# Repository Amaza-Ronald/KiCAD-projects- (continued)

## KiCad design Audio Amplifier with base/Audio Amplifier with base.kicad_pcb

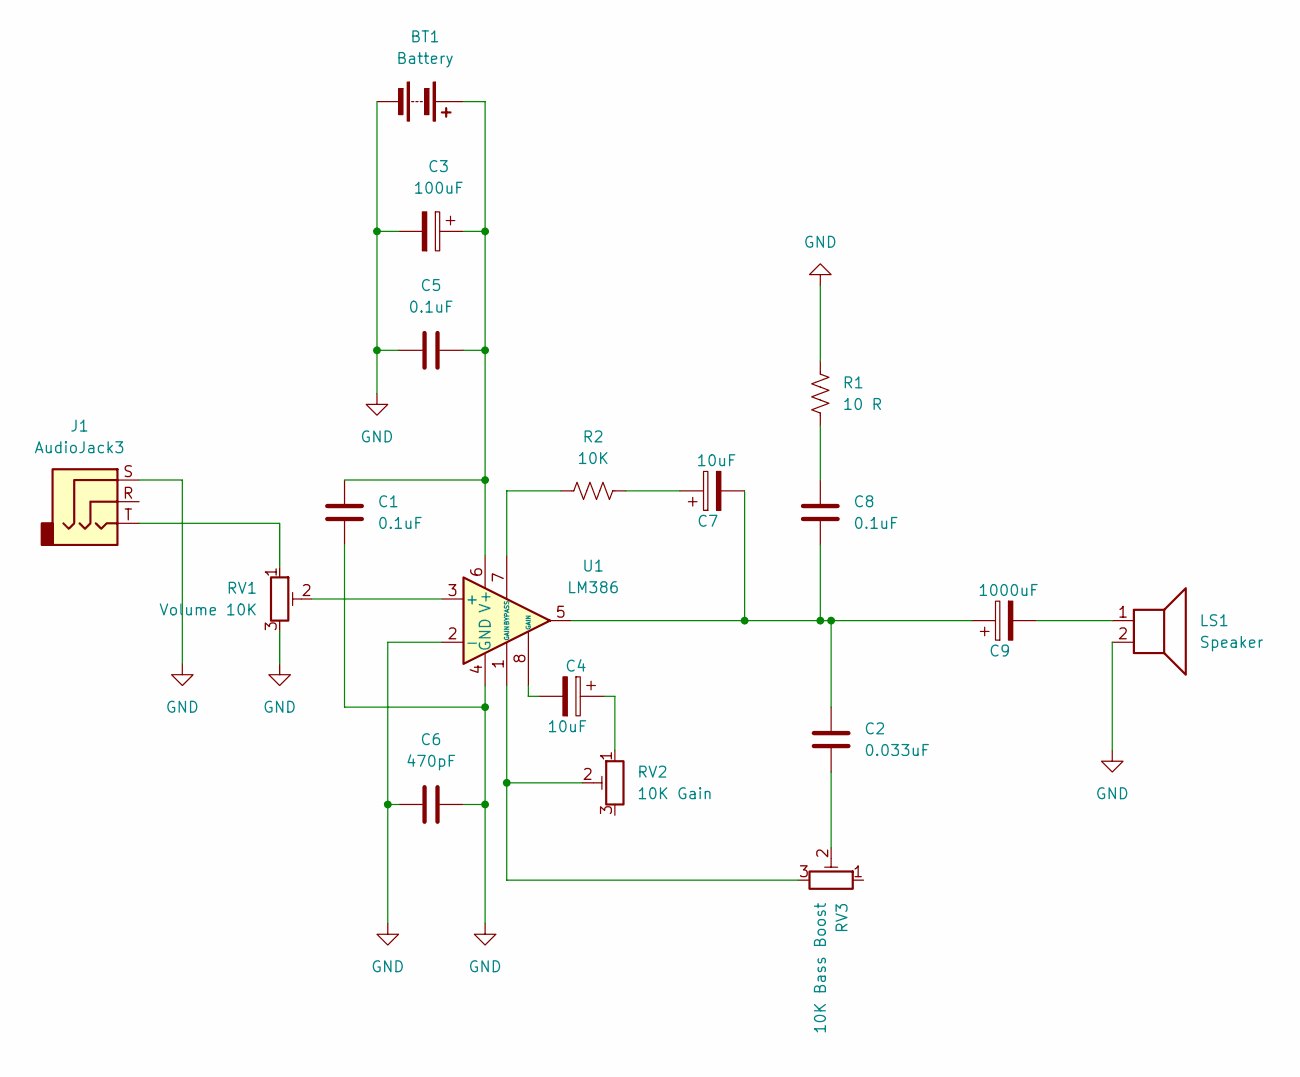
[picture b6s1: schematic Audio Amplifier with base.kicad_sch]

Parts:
BT1: Battery; Battery_Panasonic_CR1025-VSK_Vertical_CircularHoles
C1, C5, C8: 0.1uF; C_Disc_D16.0mm_W5.0mm_P7.50mm
C2: 0.033uF; C_Disc_D16.0mm_W5.0mm_P7.50mm
C3: 100uF; CP_Radial_D8.0mm_P3.50mm
C4, C7: 10uF; CP_Radial_D8.0mm_P3.50mm
C6: 470pF; C_Disc_D16.0mm_W5.0mm_P7.50mm
C9: 1000uF; CP_Radial_D8.0mm_P3.50mm
J1: AudioJack3; Jack_3.5mm_CUI_SJ1-3513N_Horizontal
LS1: Speaker; TerminalBlock_bornier-2_P5.08mm
R1: 10 R; R_Axial_DIN0207_L6.3mm_D2.5mm_P7.62mm_Horizontal
R2: 10K; R_Axial_DIN0207_L6.3mm_D2.5mm_P7.62mm_Horizontal
RV1: Volume 10K; Potentiometer_Bourns_3266X_Horizontal
RV2: 10K Gain; Potentiometer_Bourns_3266X_Horizontal
RV3: 10K Bass Boost; Potentiometer_Bourns_3266X_Horizontal
U1: LM386; DIP-8_W7.62mm_Socket_LongPads

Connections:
GND: BT1.2 (-), C1.2, C3.2, C5.2, C6.1, C6.2, J1.S, LS1.2, R1.2, RV1.3, U1.2 (-), U1.4 (GND)
unnamed: BT1.1 (+), C1.1, C3.1, C5.1, U1.6 (V+)
unnamed: C2.1, RV3.2
unnamed: C2.2, C7.2, C8.2, C9.1, U1.5
unnamed: C4.1, RV2.1
unnamed: C4.2, U1.8 (GAIN)
unnamed: C7.1, R2.1
unnamed: C8.1, R1.1
unnamed: C9.2, LS1.1
unnamed: J1.T, RV1.1
unnamed: RV2.2, RV3.3, U1.1 (GAIN)
unnamed: RV1.2, U1.3 (+)
unnamed: R2.2, U1.7 (BYPASS)

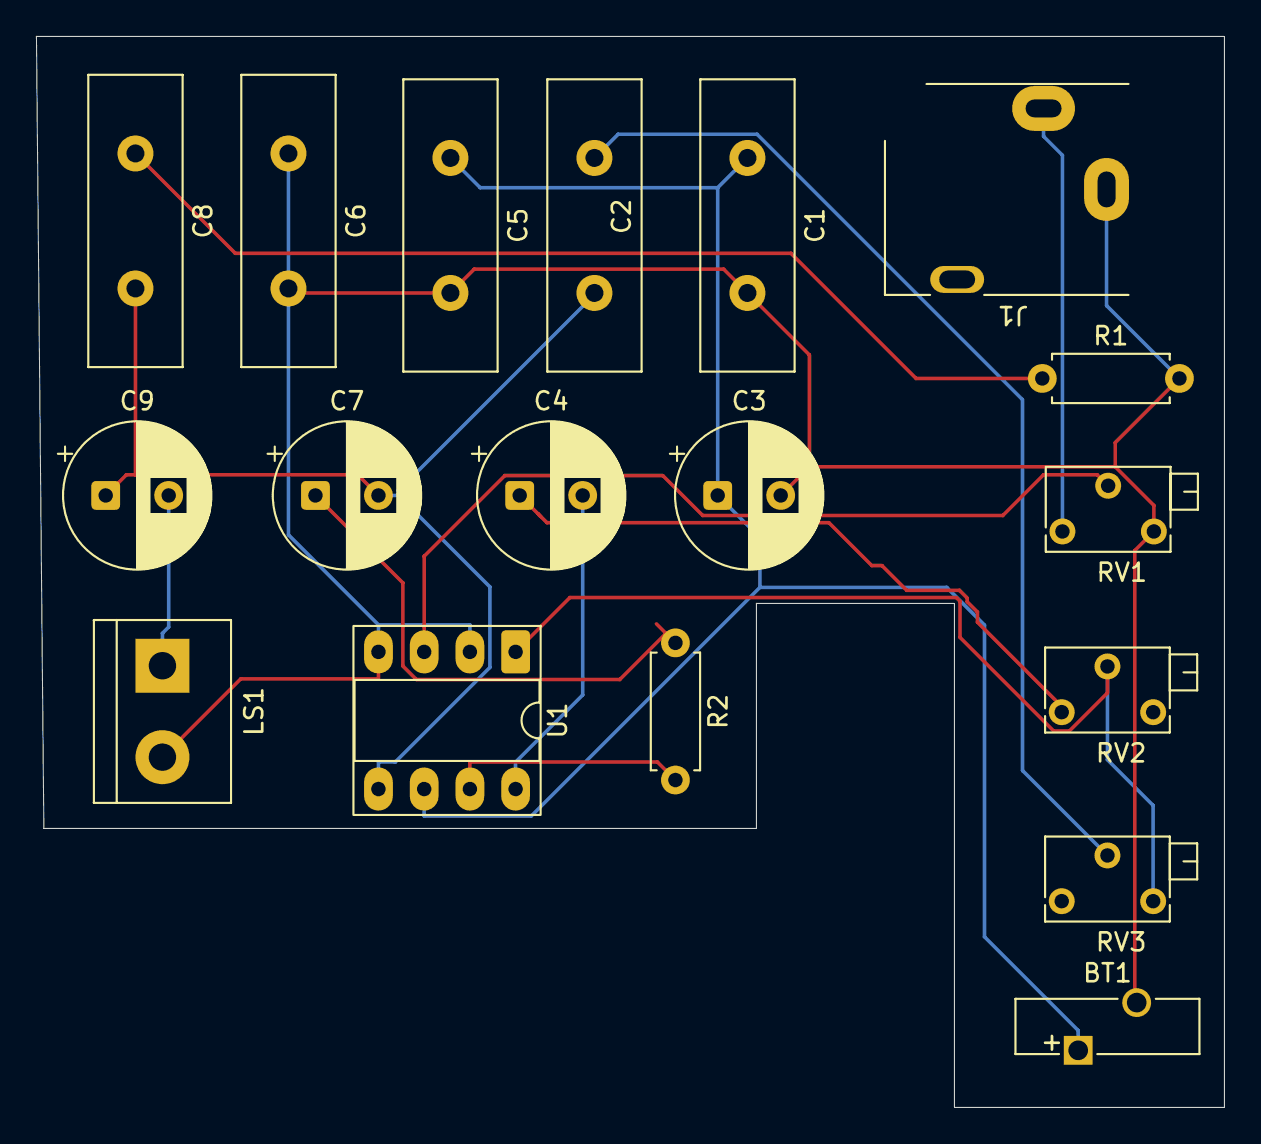
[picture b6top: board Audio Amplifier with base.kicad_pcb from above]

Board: 2 copper layers, 66.0 x 59.5 mm, 18 parts (0 on the bottom side), 13 nets.

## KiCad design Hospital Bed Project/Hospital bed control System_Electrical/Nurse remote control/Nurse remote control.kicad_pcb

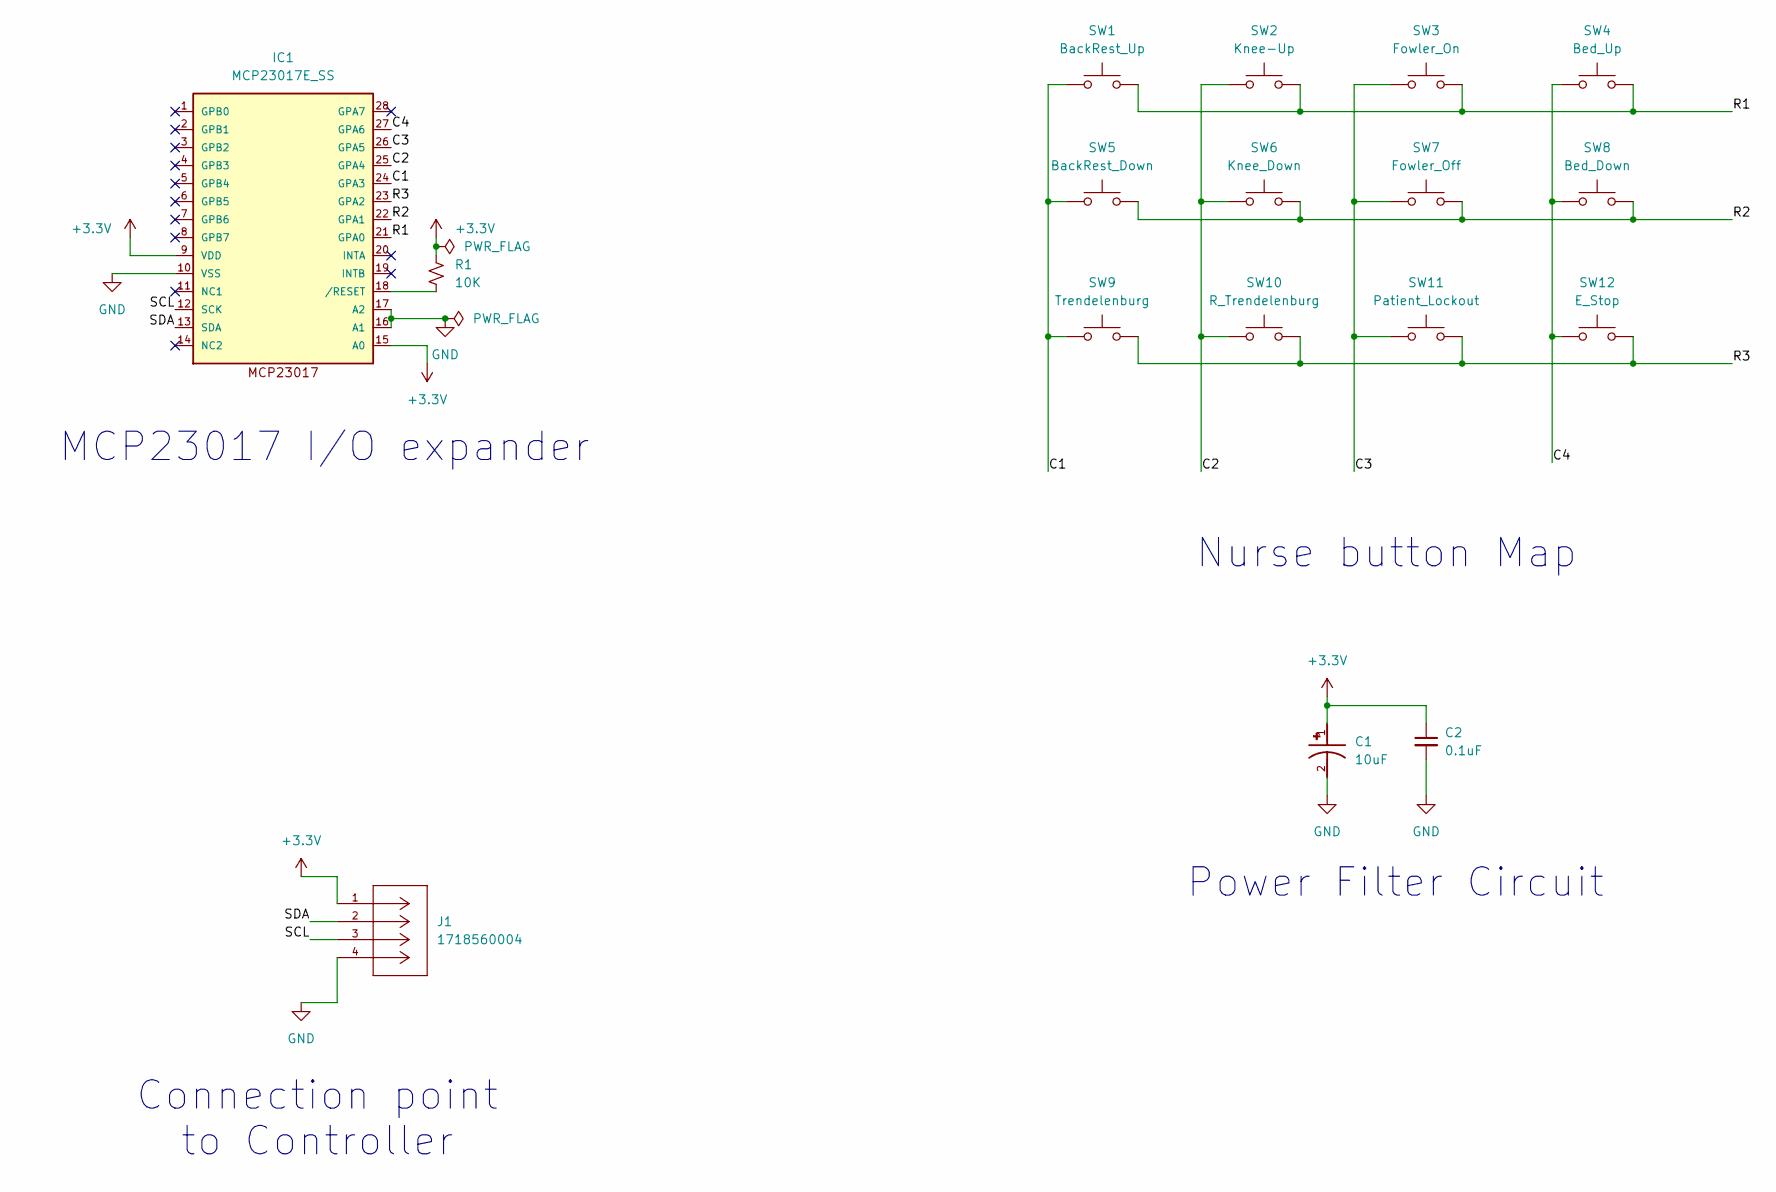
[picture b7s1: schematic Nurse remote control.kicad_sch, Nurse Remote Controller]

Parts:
C1: 10uF; CAP_EEFSX0D221ER; PARTREV 1-Oct-19
C2: 0.1uF; C_0603_1608Metric
IC1: MCP23017E_SS; SSOP28
J1: 1718560004; CONN04_1718560004_MOL; MANUFACTURER_PART_NUMBER 1718560004
R1: 10K; R_0603_1608Metric
SW1: BackRest_Up; SW_PUSH_6mm
SW2: Knee-Up; SW_PUSH_6mm
SW3: Fowler_On; SW_PUSH_6mm
SW4: Bed_Up; SW_PUSH_6mm
SW5: BackRest_Down; SW_PUSH_6mm
SW6: Knee_Down; SW_PUSH_6mm
SW7: Fowler_Off; SW_PUSH_6mm
SW8: Bed_Down; SW_PUSH_6mm
SW9: Trendelenburg; SW_PUSH_6mm
SW10: R_Trendelenburg; SW_PUSH_6mm
SW11: Patient_Lockout; SW_PUSH_6mm
SW12: E_Stop; SW_PUSH_6mm

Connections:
+3.3V: C1.1, C2.1, IC1.9 (VDD), IC1.15 (A0), J1.1, R1.1
/C1: IC1.24 (GPA3), SW1.1, SW5.1, SW9.1
/C2: IC1.25 (GPA4), SW2.1, SW6.1, SW10.1
/C3: IC1.26 (GPA5), SW3.1, SW7.1, SW11.1
/C4: IC1.27 (GPA6), SW4.1, SW8.1, SW12.1
/R1: IC1.21 (GPA0), SW1.2, SW2.2, SW3.2, SW4.2
/R2: IC1.22 (GPA1), SW5.2, SW6.2, SW7.2, SW8.2
/R3: IC1.23 (GPA2), SW9.2, SW10.2, SW11.2, SW12.2
/SCL: IC1.12 (SCK), J1.3
/SDA: IC1.13 (SDA), J1.2
GND: C1.2, C2.2, IC1.10 (VSS), IC1.16 (A1), IC1.17 (A2), J1.4
unnamed: IC1.18 (/RESET), R1.2

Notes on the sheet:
Power Filter Circuit
MCP23017 I/O expander
Nurse button Map
Connection point to Controller

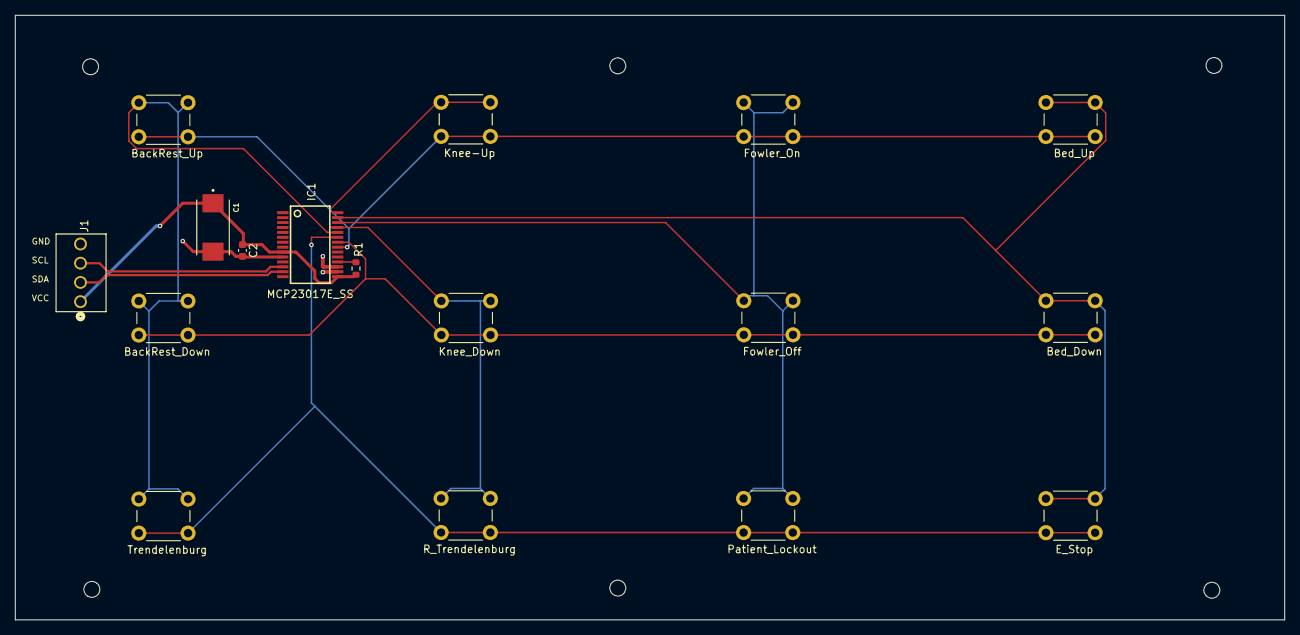
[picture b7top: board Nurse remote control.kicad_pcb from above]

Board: 2 copper layers, 167.6 x 79.8 mm, 23 parts (0 on the bottom side), 12 nets.

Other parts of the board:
REF1, REF2, REF3, REF4, REF5, REF6: MountingHole_2.1mm

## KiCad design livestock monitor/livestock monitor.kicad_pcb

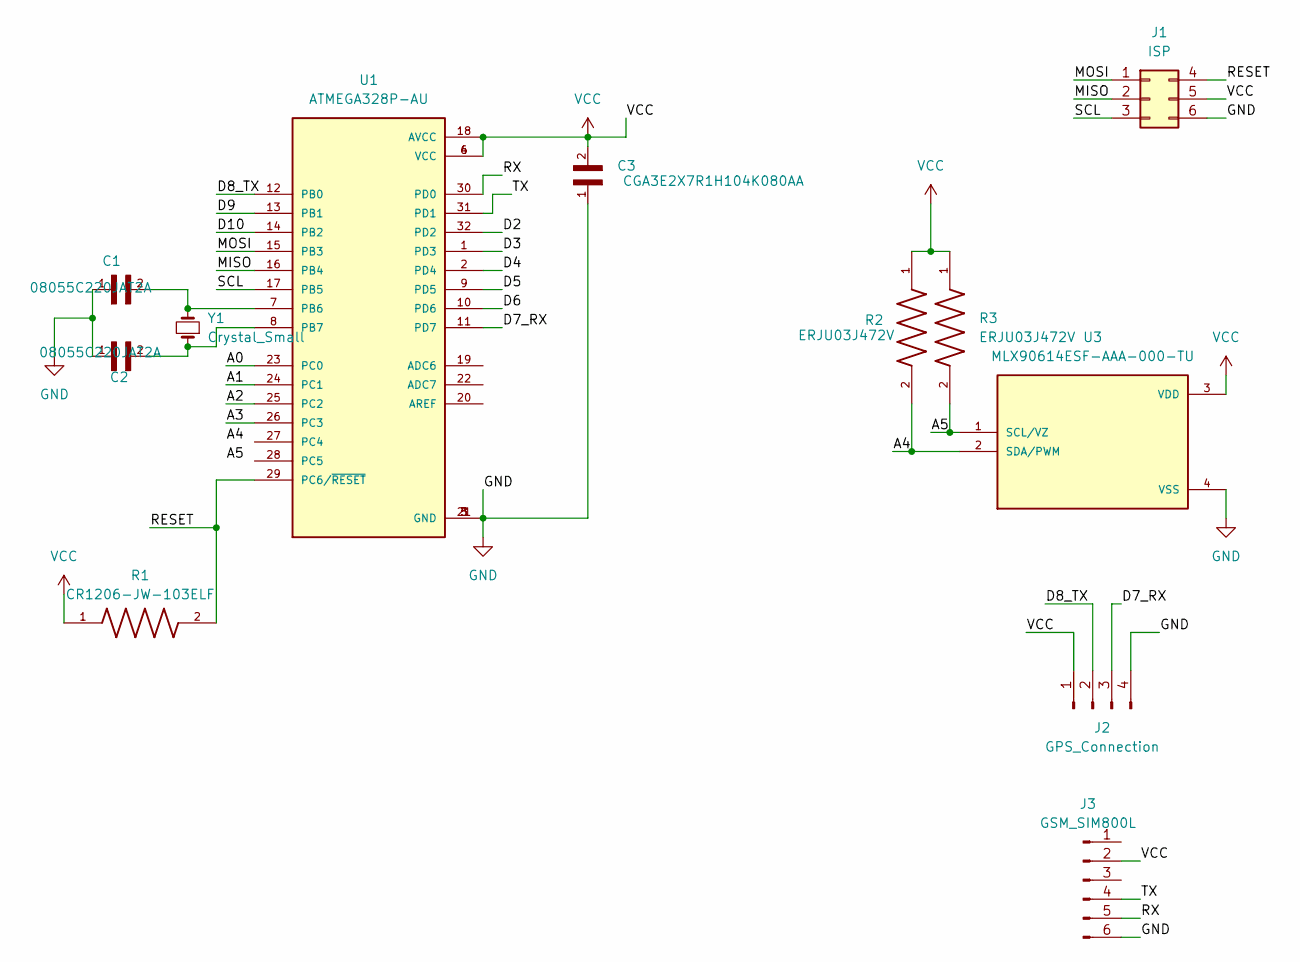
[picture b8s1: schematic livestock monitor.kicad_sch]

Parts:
C1, C2: 08055C220JAT2A; CAPC2012X94N
C3: CGA3E2X7R1H104K080AA; CAPC1608X90N; DigiKey_Part_Number 445-5666-2-ND
J1: ISP; PinHeader_2x03_P2.54mm_Vertical
J2: GPS_Connection; PinHeader_1x04_P2.54mm_Vertical
J3: GSM_SIM800L; PinHeader_1x06_P2.54mm_Vertical
R1: CR1206-JW-103ELF; RESC3216X75N
R2, R3: ERJU03J472V; RES_ERJU03J472V; PARTREV 3/1/2020
U1: ATMEGA328P-AU; QFP80P900X900X120-32N; PARTREV 8271A
U3: MLX90614ESF-AAA-000-TU; TO254P912H435-4; PARTREV 13
Y1: Crystal_Small; Crystal_SMD_3215-2Pin_3.2x1.5mm

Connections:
/A0: U1.23 (PC0)
/A1: U1.24 (PC1)
/A2: U1.25 (PC2)
/A3: U1.26 (PC3)
/A4: R2.2, U3.2 (SDA/PWM)
/A5: R3.2, U3.1 (SCL/VZ)
/D2: U1.32 (PD2)
/D3: U1.1 (PD3)
/D4: U1.2 (PD4)
/D5: U1.9 (PD5)
/D6: U1.10 (PD6)
/D7_RX: J2.3, U1.11 (PD7)
/D8_TX: J2.2, U1.12 (PB0)
/D9: U1.13 (PB1)
/D10: U1.14 (PB2)
/MISO: J1.2, U1.16 (PB4)
/MOSI: J1.1, U1.15 (PB3)
/RESET: J1.4, R1.2, U1.29 (PC6/~RESET)
/RX: J3.5, U1.30 (PD0)
/SCL: J1.3, U1.17 (PB5)
/TX: J3.4, U1.31 (PD1)
GND: C1.1, C2.1, C3.1, J1.6, J2.4, J3.6, U1.3 (GND), U1.5 (GND), U1.21 (GND), U3.4 (VSS)
unnamed: C1.2, U1.7 (PB6), Y1.2
unnamed: C2.2, U1.8 (PB7), Y1.1
VCC: C3.2, J1.5, J2.1, J3.2, R1.1, R2.1, R3.1, U1.4 (VCC), U1.6 (VCC), U1.18 (AVCC), U3.3 (VDD)

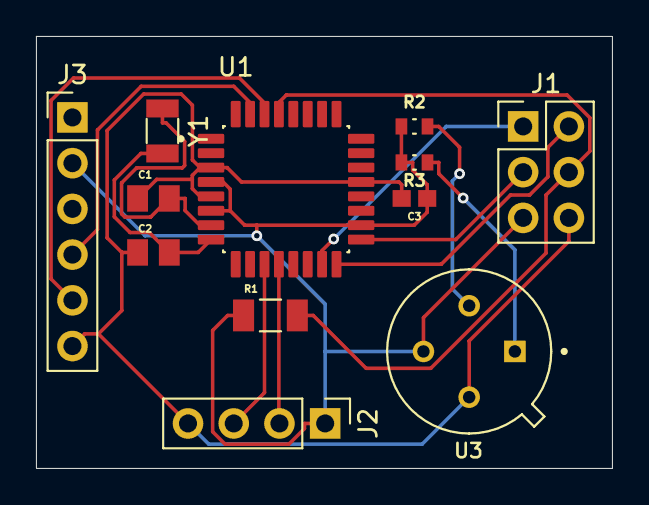
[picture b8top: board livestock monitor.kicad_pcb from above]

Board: 2 copper layers, 32.0 x 24.0 mm, 12 parts (0 on the bottom side), 14 nets.

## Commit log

2026-02-04 My Projects Folder Added
